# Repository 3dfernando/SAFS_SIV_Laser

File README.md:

# FSIV - A high-speed Focusing Schlieren Velocimetry system

Big thanks to MazinLab (https://github.com/MazinLab/BigPulse) for publishing their laser driver! It enabled us to build this project at a very low cost!

## Samples

Here's a couple samples of the images acquired with this light source:

| Shear Layer of a M=0.98 jet (dt=800 ns) | Boundary Layer of a M=0.91 plug nozzle (dt=800 ns) |
|---|---|
|  |  |
| **Microjet SBLI at M=2 (dt=800 ns)** | |
|  | |

## Project Description

Velocimetry in high-speed aerodynamics (supersonic flows, more specifically) is very challenging. The flow velocities are so high that you need a high-frequency light source to be able to capture all the dynamics of the flow. More challengingly, the high velocities also bring the required delay between consecutive frames to order <500ns, requiring two light sources and the staggering of pulses.

For Particle Image Velocimetry (PIV), the laser must deliver sufficient pulse energy to scatter enough light onto the camera sensor — typically ≥10 mJ/pulse. Combined with the high-speed requirement, a suitable light source can exceed $200,000 USD, making this research prohibitively expensive even for well-funded laboratories. However, for schlieren imaging the amount of light required is much lower - about 10nJ/pulse are sufficient to fully illuminate the camera sensor and overcome the light losses. Thus, we developed a light source capable of ~400nJ/pulse and 30ns pulse width, which is adequate for most schlieren needs. 

Convective velocity — the velocity of turbulent structures and a key contributor to noise sources in aeroacoustics — requires at least two consecutive PIV velocity field measurements to be estimated from velocity data. However, if the flow structure can be captured directly through focusing schlieren (which images density gradients in the flow), it is possible to measure convective velocity directly by cross-correlating consecutive schlieren images.

Further, the double-pulsed schlieren images can also be processed with Online Dynamic Mode Decomposition (ODMD) to extract the coherent behavior of the flow at very high frequencies, limited by the Nyquist frequency based on the inter-frame pulse delay dt (typically <300 ns). For example, at dt=300 ns, this enables the observation of coherent structures up to ~1.7 MHz — beyond the capability of state-of-the-art high-speed cameras — at full camera resolution.

With our SAFS-SIV system, we are able to build a light source for under USD 1,000 capable of 50 kHz double-pulses with a 30 ns pulse width. At supersonic speeds, a 30 ns pulse corresponds to only ~2 μm of particle displacement, nearly eliminating motion blur. This low-cost device opens the door to high-speed flow diagnostics for a much broader range of research groups and institutions.

## Revision Notes

The R00 project was originally a double-pulse driver with two individual boards with their own lasers, both focused on a fiber. We noticed that this design, although effective, was a bit more expensive to build and had a disadvantage for advanced processing techniques because the speckle pattern of the fiber was a bit different for each laser, since they optically were coupled differently. 

We decided to revise the circuit (R01 board) to fire the same physical laser twice in consecutive pulses coming from two different capacitor banks. To accomplish this, we needed to add a new fast SiC diode (FC06020E-3), which ensures the capacitor banks discharge separately. This design produces significantly more uniform images; though there is still a small variation of ~1% of brightness between the two pulses due to the capacitor banks having a tolerance. This effect is already minimized by having 6 capacitors, which reduces the tolerance of the bank.

The R01 design has also significantly improved thermal performance. The high-power resistors R1/R3 (10 Ohm) and R11/R12/R16/R17 (560 Ohm) were added as two series resistors to replace the original 20 Ohm and 1200 Ohm resistors. This increases the thermal dissipation area and enables the driver to operate for longer at higher repetition rates.

Note the R01 board is a 4-layer board to improve RF shielding as the high currents from discharging the capacitor bank were, during our development effort, triggering the other capacitor bank. We believe the updated design doesn't have this issue anymore.

## Driver Picture (R01)

This is the new driver. More pictures coming soon!

## Driver Picture (R00)

**This is the old driver!** Below a photograph of our laser drivers forming a double-pulse system in a 1.0 mm fiber optic:

A closer view of the PCB design:

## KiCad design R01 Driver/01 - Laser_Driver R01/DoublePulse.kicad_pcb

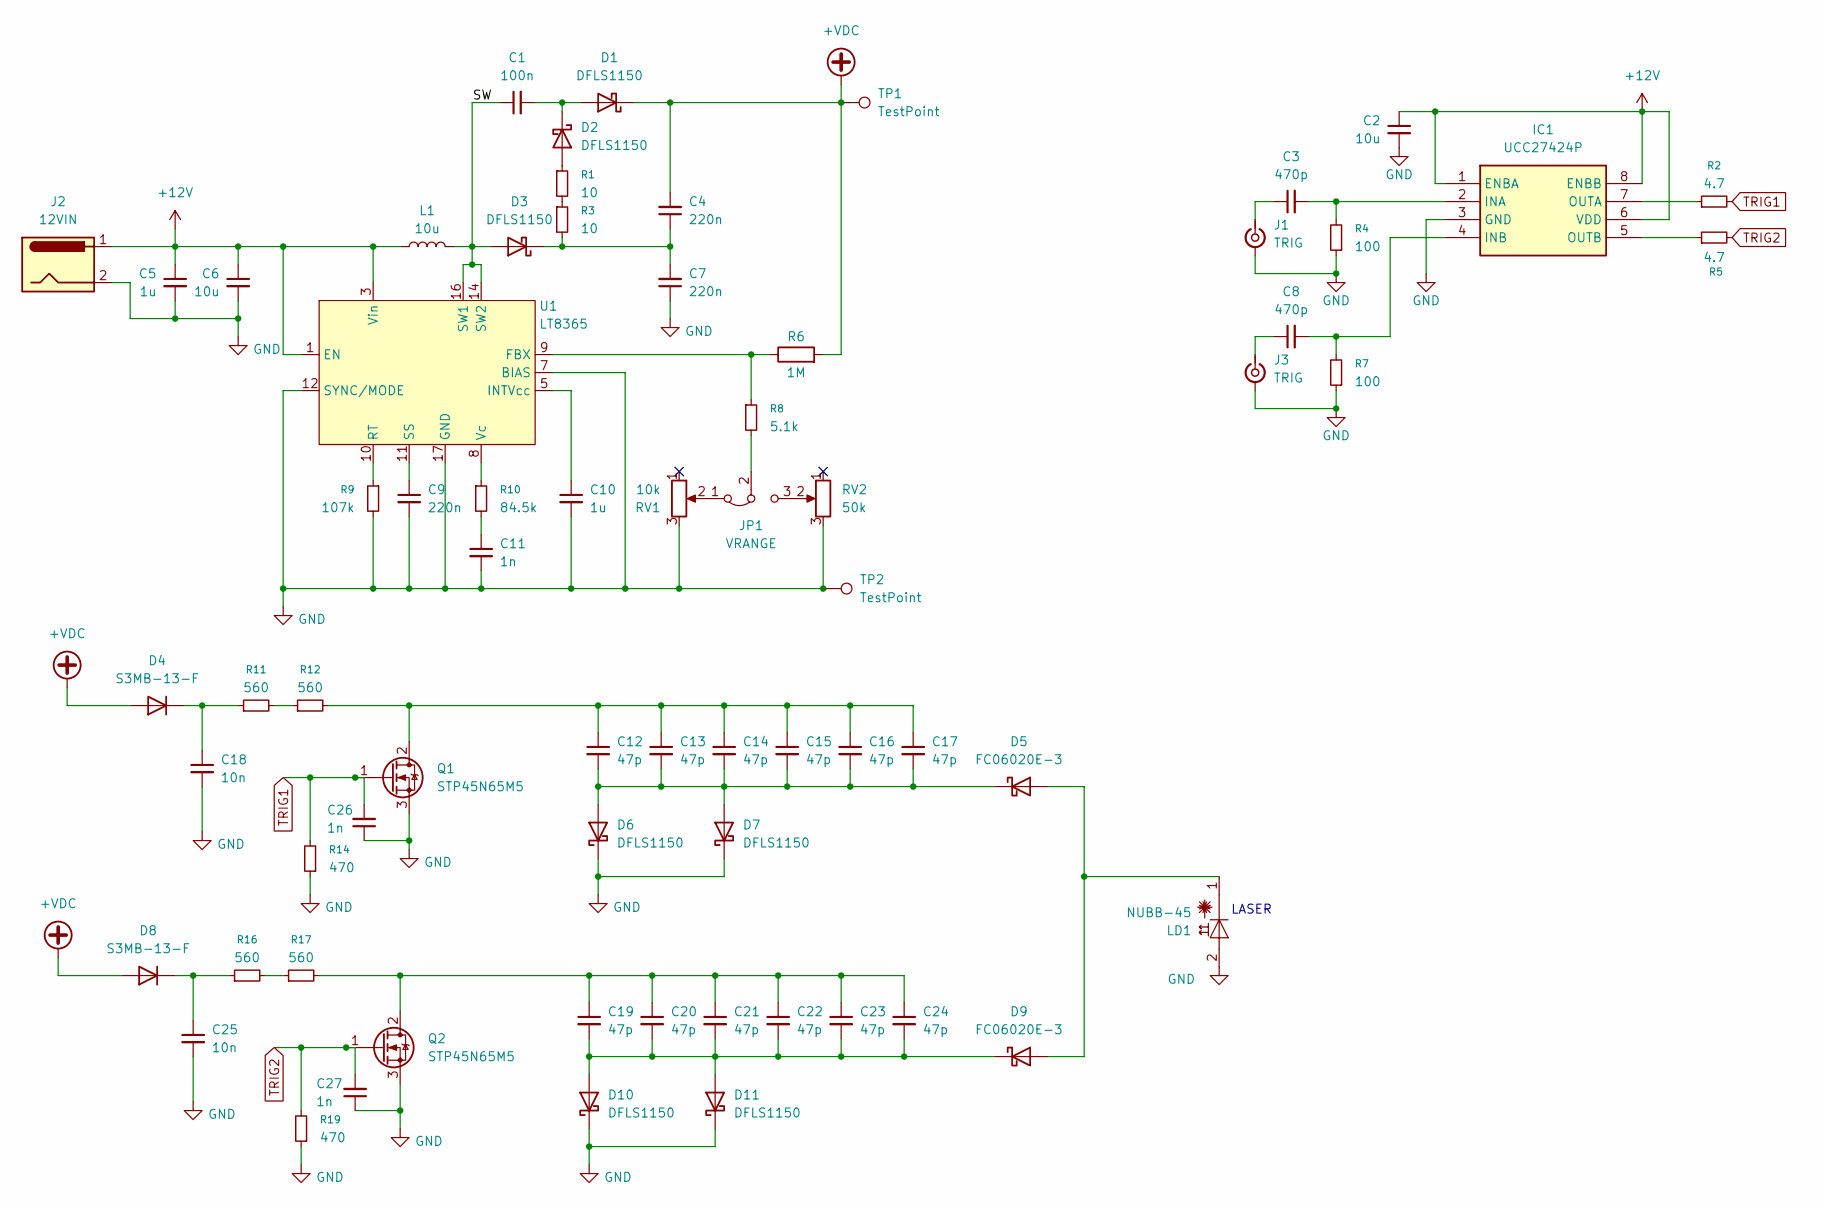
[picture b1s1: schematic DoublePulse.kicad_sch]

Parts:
C1: 100n; C_1210_3225Metric; DIGIKEY_PN 399-13490-1-ND
C2, C6: 10u; C_2220_5750Metric; DIGIKEY_PN 445-CGA9N3X7R1H106K230KBCT-ND
C3, C8: 470p; C_0603_1608Metric; DIGIKEY_PN 399-C0603C102K5RACTUCT-ND
C4, C7: 220n; C_2220_5750Metric; DIGIKEY_PN 490-3520-1-ND
C5: 1u; C_2220_5750Metric; DIGIKEY_PN 311-2069-1-ND
C9: 220n; C_0603_1608Metric; DIGIKEY_PN 490-5402-1-ND
C10: 1u; C_0603_1608Metric; DIGIKEY_PN 1276-1946-1-ND
C11, C26, C27: 1n; C_0603_1608Metric; DIGIKEY_PN 399-C0603C102K5RACTUCT-ND
C12, C13, C14, C15, C16, C17, C19, C20, C21, C22, C23, C24: 47p; C_1210_3225Metric; DIGIKEY_PN 720-1040-1-ND
C18, C25: 10n; C_1210_3225Metric; DIGIKEY_PN 709-VPDF102W103K1GV001ECT-ND
D1, D2, D3, D6, D7, D10, D11: DFLS1150; D_PowerDI-123; DIGIKEY_PN DFLS1150Q-7DICT-ND
D4, D8: S3MB-13-F; D_SMB; DIGIKEY_PN S3MB-FDICT-ND
D5, D9: FC06020E-3; TO-247-3_Vertical; DIGIKEY_PN 5700-FC06020E-3-ND
IC1: UCC27424P; DIP-8_W7.62mm; Mouser Part Number 595-UCC27424P
J1, J3: TRIG; SMA_Amphenol_132134-10_Vertical; DIGIKEY_PN 132134-10
J2: 12VIN; BarrelJack_Wuerth_694106106102_2.0x5.5mm; DIGIKEY_PN 732-5929-1-ND
JP1: VRANGE; SolderJumper-3_P1.3mm_Bridged2Bar12_Pad1.0x1.5mm
L1: 10u; L_Wurth_WE-LQSH-4020; DIGIKEY_PN 732-3336-1-ND
LD1: NUBB-45; NUBB45
Q1, Q2: STP45N65M5; LCSC C672233
R1, R3: 10; R_2512_6332Metric_Pad1.40x3.35mm_HandSolder; DIGIKEY_PN 118-CHP2512AFX-10R0ELFCT-ND
R2, R5: 4.7; R_1206_3216Metric_Pad1.30x1.75mm_HandSolder; DIGIKEY_PN RMCF1206FT4R70CT-ND
R4, R7: 100; R_0603_1608Metric; DIGIKEY_PN 764-FC0603E50R0BTBST1CT-ND
R6: 1M; R_0603_1608Metric; DIGIKEY_PN 2019-RN73H1JTTD1004B25CT-ND
R8: 5.1k; R_0603_1608Metric; DIGIKEY_PN RMCF0603FT5K10CT-ND
R9: 107k; R_0603_1608Metric; DIGIKEY_PN 311-107KHRCT-ND
R10: 84.5k; R_0603_1608Metric; DIGIKEY_PN 311-84.5KHRCT-ND
R11, R12, R16, R17: 560; R_2512_6332Metric_Pad1.40x3.35mm_HandSolder; DIGIKEY_PN A121273CT-ND
R14, R19: 470; R_1210_3225Metric; DIGIKEY_PN 13-RC1210FR-07470RLCT-ND
RV1: 10k; Potentiometer_Bourns_3314S_Horizontal; DIGIKEY_PN 3314J-103ECT-ND
RV2: 50k; Potentiometer_Bourns_3314S_Horizontal; DIGIKEY_PN 3314J-503ECT-ND
TP1, TP2: TestPoint; PinHeader_1x01_P2.54mm_Vertical; LCSC C238118
U1: LT8365; Analog_MSOP-12-16-1EP_3x4.039mm_P0.5mm_EP1.651x2.845mm_Ther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; DIGIKEY_PN 505-LT8365EMSE#TRPBFCT-ND

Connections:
+12V: C2.1, C5.1, C6.1, IC1.1 (ENBA), IC1.6 (VDD), IC1.8 (ENBB), J2.1, L1.1, U1.1 (EN), U1.3 (Vin)
+VDC: C4.2, D1.1 (K), D4.2 (A), D8.2 (A), R6.2, TP1.1 (1_1)
/SW: C1.1, D3.2 (A), L1.2, U1.14 (SW2), U1.16 (SW1)
GND: C2.2, C5.2, C6.2, C7.1, C9.2, C10.2, C11.2, C18.2, C25.2, C26.1, C27.1, D6.1 (K), D7.1 (K), D10.1 (K), D11.1 (K), IC1.3 (GND), J1.2 (Ext), J2.2, J3.2 (Ext), LD1.2 (A), Q1.3 (S), Q2.3 (S), R4.1, R7.1, R9.2, R14.1, R19.1, RV1.3, RV2.3, TP2.1 (1_1), U1.7 (BIAS), U1.12 (SYNC/MODE), U1.17 (GND)
unnamed: C11.1, R10.2
unnamed: C1.2, D1.2 (A), D2.1 (K)
unnamed: D2.2 (A), R1.1
unnamed: C4.1, C7.2, D3.1 (K), R3.2
unnamed: C18.1, D4.1 (K), R11.1
unnamed: D5.1 (A), D9.3 (A), LD1.1 (C)
unnamed: C12.2, C13.2, C14.2, C15.2, C16.2, C17.2, D5.2 (K), D6.2 (A), D7.2 (A)
unnamed: C25.1, D8.1 (K), R16.1
unnamed: C19.2, C20.2, C21.2, C22.2, C23.2, C24.2, D9.2 (K), D10.2 (A), D11.2 (A)
unnamed: C3.2, IC1.2 (INA), R4.2
unnamed: C8.2, IC1.4 (INB), R7.2
unnamed: IC1.7 (OUTA), R2.1
unnamed: IC1.5 (OUTB), R5.1
unnamed: C3.1, J1.1 (In)
unnamed: C8.1, J3.1 (In)
unnamed: JP1.1 (A), RV1.2
unnamed: JP1.3 (B), RV2.2
unnamed: JP1.2 (C), R8.2
unnamed: C12.1, C13.1, C14.1, C15.1, C16.1, C17.1, Q1.2 (D), R12.2
unnamed: C19.1, C20.1, C21.1, C22.1, C23.1, C24.1, Q2.2 (D), R17.2
unnamed: R1.2, R3.1
unnamed: R11.2, R12.1
unnamed: R16.2, R17.1
unnamed: R6.1, R8.1, U1.9 (FBX)
unnamed: C10.1, U1.5 (INTVcc)
unnamed: R9.1, U1.10 (RT)
unnamed: C9.1, U1.11 (SS)
unnamed: R10.1, U1.8 (Vc)
TRIG1: C26.2, Q1.1 (G), R2.2, R14.2
TRIG2: C27.2, Q2.1 (G), R5.2, R19.2

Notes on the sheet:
LASER

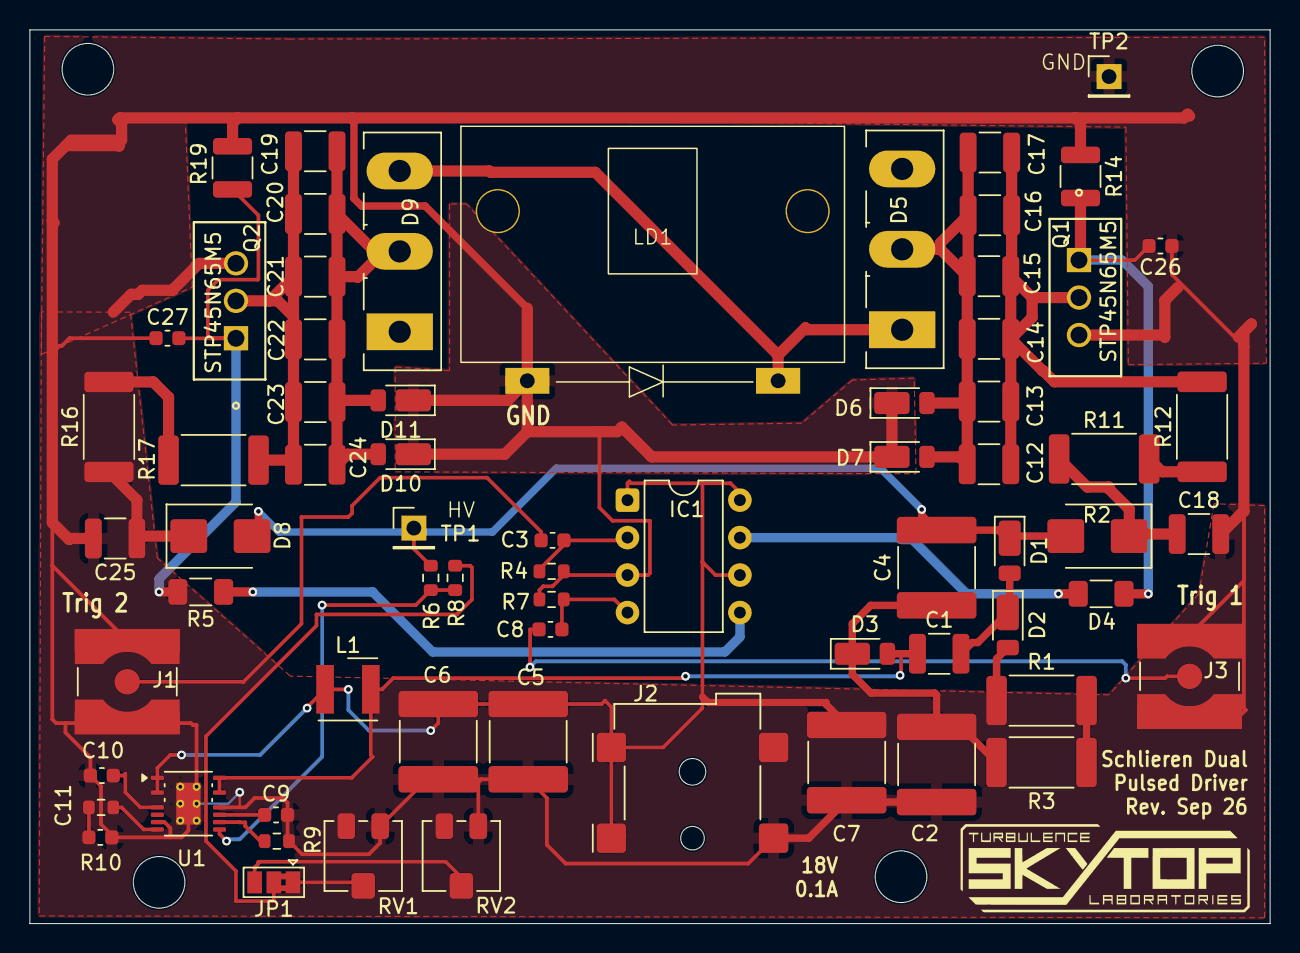
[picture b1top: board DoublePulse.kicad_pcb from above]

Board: 4 copper layers, 84.1 x 60.6 mm, 72 parts (0 on the bottom side), 34 nets.

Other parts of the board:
H**: 1/4 20; quarter-twenty
H**#2, H**#3, H**#4: 1/4 20; quarter-twenty

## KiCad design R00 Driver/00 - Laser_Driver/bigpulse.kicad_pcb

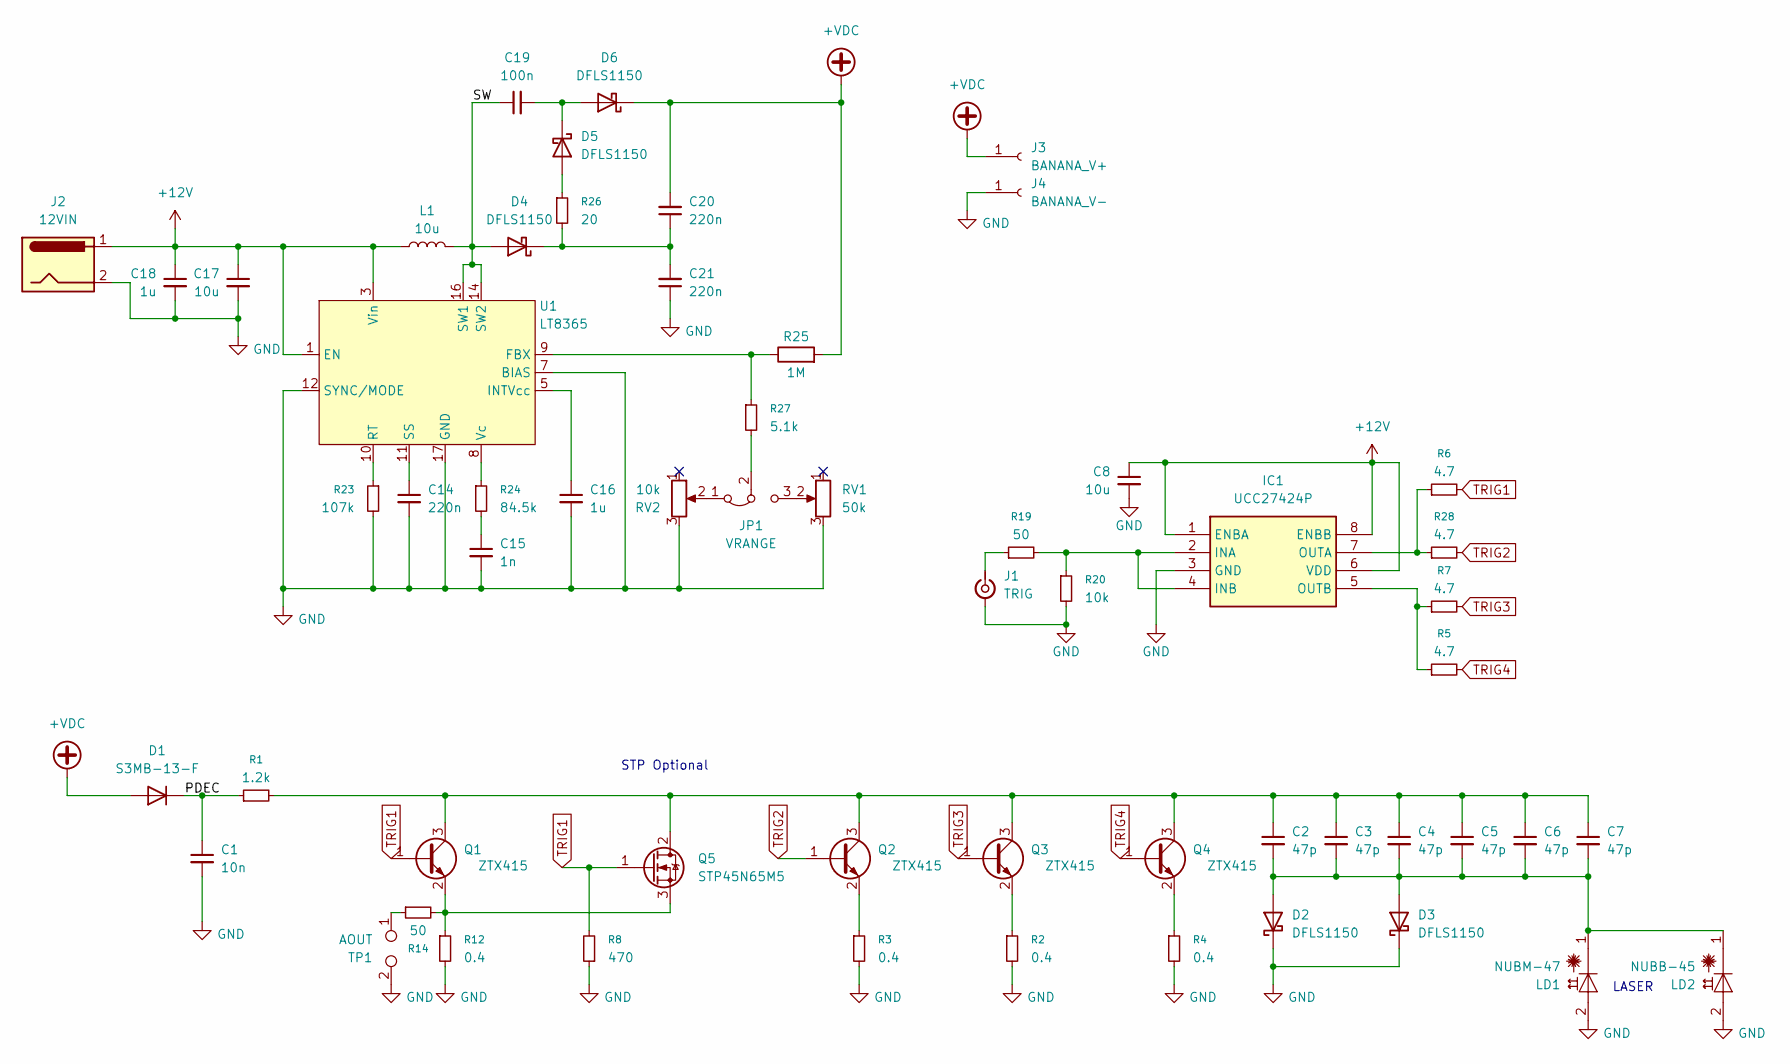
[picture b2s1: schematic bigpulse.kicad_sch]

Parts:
C1: 10n; C_1210_3225Metric; DIGIKEY_PN 709-VPDF102W103K1GV001ECT-ND
C2, C3, C4, C5, C6, C7: 47p; C_1210_3225Metric; DIGIKEY_PN 720-1040-1-ND
C8, C17: 10u; C_2220_5750Metric; DIGIKEY_PN 478-KGM55DR72A106MVCT-ND
C14: 220n; C_0603_1608Metric; DIGIKEY_PN 490-5402-1-ND
C15: 1n; C_0603_1608Metric; DIGIKEY_PN 399-C0603C102K5RACTUCT-ND
C16: 1u; C_0603_1608Metric; DIGIKEY_PN 1276-1946-1-ND
C18: 1u; C_2220_5750Metric; DIGIKEY_PN 478-KGF55DR72J105KVCT-ND
C19: 100n; C_1210_3225Metric; DIGIKEY_PN 445-2300-1-ND
C20, C21: 220n; C_2220_5750Metric; DIGIKEY_PN 490-3520-1-ND
D1: S3MB-13-F; D_SMB; DIGIKEY_PN S3MB-FDICT-ND
D2, D3, D4, D5, D6: DFLS1150; D_PowerDI-123; DIGIKEY_PN DFLS1150Q-7DICT-ND
IC1: UCC27424P; DIP-8_W7.62mm; Mouser Part Number 595-UCC27424P
J1: TRIG; SMA_Amphenol_132134-10_Vertical; DIGIKEY_PN 132134-10
J2: 12VIN; BarrelJack_Wuerth_694106106102_2.0x5.5mm; DIGIKEY_PN 732-5929-1-ND
J3: BANANA_V+; MountingHole_3.7mm_Pad_Via; DIGIKEY_PN J10125-ND
J4: BANANA_V-; MountingHole_3.7mm_Pad_Via; DIGIKEY_PN J10126-ND
JP1: VRANGE; SolderJumper-3_P1.3mm_Bridged2Bar12_Pad1.0x1.5mm
L1: 10u; L_Wurth_WE-LQSH-4020; DIGIKEY_PN 732-3336-1-ND
LD1: NUBM-47; NUBM44
LD2: NUBB-45; NUBB45
Q1, Q2, Q3, Q4: ZTX415; TO-92; DIGIKEY_PN ZTX415-ND
Q5: STP45N65M5; LCSC C672233
R1: 1.2k; R_2512_6332Metric_Pad1.40x3.35mm_HandSolder; LCSC C719184
R2, R3, R4, R12: 0.4; R_1206_3216Metric_Pad1.30x1.75mm_HandSolder; LCSC C719184
R5, R6, R7, R28: 4.7; R_1206_3216Metric_Pad1.30x1.75mm_HandSolder; LCSC C719184
R8: 470; R_1210_3225Metric; LCSC C719184
R14, R19: 50; R_0603_1608Metric; DIGIKEY_PN 764-FC0603E50R0BTBST1CT-ND
R20: 10k; R_0603_1608Metric; DIGIKEY_PN RMCF0603JT10K0CT-ND
R23: 107k; R_0603_1608Metric; DIGIKEY_PN 311-107KHRCT-ND
R24: 84.5k; R_0603_1608Metric; DIGIKEY_PN 311-84.5KHRCT-ND
R25: 1M; R_0603_1608Metric; DIGIKEY_PN 2019-RN73H1JTTD1004B25CT-ND
R26: 20; R_2512_6332Metric_Pad1.40x3.35mm_HandSolder; LCSC C719184
R27: 5.1k; R_0603_1608Metric; LCSC C719184
RV1: 50k; Potentiometer_Bourns_3314S_Horizontal; DIGIKEY_PN 3314J-503ECT-ND
RV2: 10k; Potentiometer_Bourns_3314S_Horizontal; DIGIKEY_PN 3314J-103ECT-ND
TP1: AOUT; SMA_Amphenol_132134-10_Vertical; DIGIKEY_PN 132134-10
U1: LT8365; Analog_MSOP-12-16-1EP_3x4.039mm_P0.5mm_EP1.651x2.845mm_Ther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; DIGIKEY_PN 505-LT8365EMSE#TRPBFCT-ND

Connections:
+12V: C8.1, C17.1, C18.1, IC1.1 (ENBA), IC1.6 (VDD), IC1.8 (ENBB), J2.1, L1.1, U1.1 (EN), U1.3 (Vin)
+VDC: C20.2, D1.2 (A), D6.1 (K), J3.1, R25.2
/PDEC: C1.1, D1.1 (K), R1.1
/SW: C19.1, D4.2 (A), L1.2, U1.14 (SW2), U1.16 (SW1)
GND: C1.2, C8.2, C14.2, C15.2, C16.2, C17.2, C18.2, C21.1, D2.1 (K), D3.1 (K), IC1.3 (GND), J1.2 (Ext), J2.2, J4.1, LD1.2 (A), LD2.2 (A), R2.2, R3.2, R4.2, R8.1, R12.2, R20.2, R23.2, RV1.3, RV2.3, TP1.2, U1.7 (BIAS), U1.12 (SYNC/MODE), U1.17 (GND)
unnamed: C15.1, R24.2
unnamed: C2.2, C3.2, C4.2, C5.2, C6.2, C7.2, D2.2 (A), D3.2 (A), LD1.1 (C), LD2.1 (C)
unnamed: C20.1, C21.2, D4.1 (K), R26.2
unnamed: D5.2 (A), R26.1
unnamed: C19.2, D5.1 (K), D6.2 (A)
unnamed: IC1.2 (INA), IC1.4 (INB), R19.2, R20.1
unnamed: IC1.7 (OUTA), R6.1, R28.1
unnamed: IC1.5 (OUTB), R5.1, R7.1
unnamed: J1.1 (In), R19.1
unnamed: JP1.1 (A), RV2.2
unnamed: JP1.3 (B), RV1.2
unnamed: JP1.2 (C), R27.2
unnamed: C2.1, C3.1, C4.1, C5.1, C6.1, C7.1, Q1.3 (C), Q2.3 (C), Q3.3 (C), Q4.3 (C), Q5.2 (D), R1.2
unnamed: Q1.2 (E), Q5.3 (S), R12.1, R14.2
unnamed: Q2.2 (E), R3.1
unnamed: Q3.2 (E), R2.1
unnamed: Q4.2 (E), R4.1
unnamed: R14.1, TP1.1
unnamed: R25.1, R27.1, U1.9 (FBX)
unnamed: C16.1, U1.5 (INTVcc)
unnamed: R23.1, U1.10 (RT)
unnamed: C14.1, U1.11 (SS)
unnamed: R24.1, U1.8 (Vc)
TRIG1: Q1.1 (B), Q5.1 (G), R6.2, R8.2
TRIG2: Q2.1 (B), R28.2
TRIG3: Q3.1 (B), R7.2
TRIG4: Q4.1 (B), R5.2

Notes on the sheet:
STP Optional
LASER

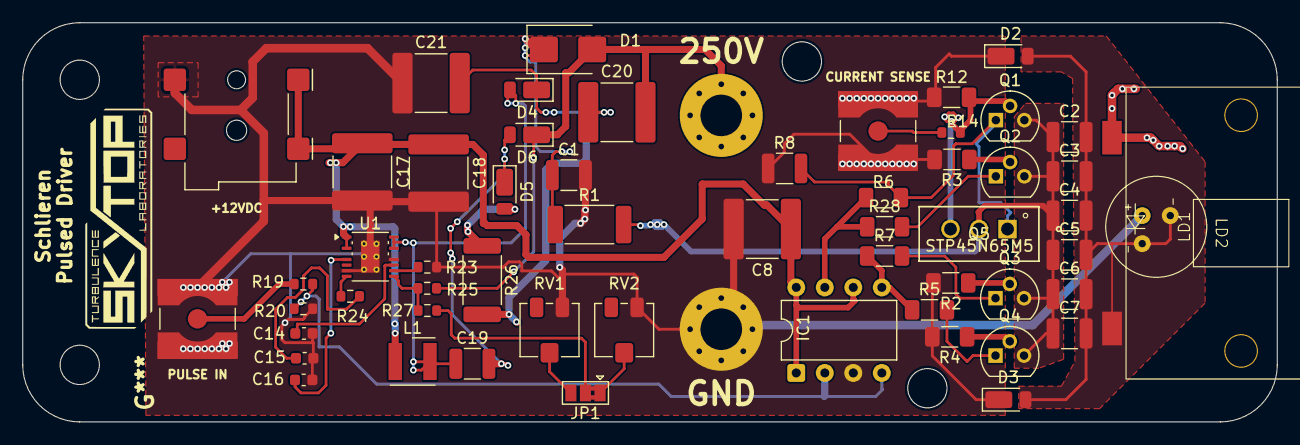
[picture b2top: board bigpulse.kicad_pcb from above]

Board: 2 copper layers, 111.8 x 35.6 mm, 61 parts (0 on the bottom side), 32 nets.

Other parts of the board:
H**: 1/4 20; quarter-twenty
H**#2, H**#3: 1/4 20; quarter-twenty

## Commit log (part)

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2026-03-06 Option for NUBB45 and Improvements
2026-03-11 Minor improvements after prototyping
    Legs of MOSFET were switched.
2026-03-11 Energy Measurements with new board
2026-06-04 Create Test.txt
    Dummy file
2026-06-04 Gif Samples of double-pulse focusing schlieren

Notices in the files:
parts and their libraries:
Copyright 2016 Accelerated Designs. All rights reserved.
